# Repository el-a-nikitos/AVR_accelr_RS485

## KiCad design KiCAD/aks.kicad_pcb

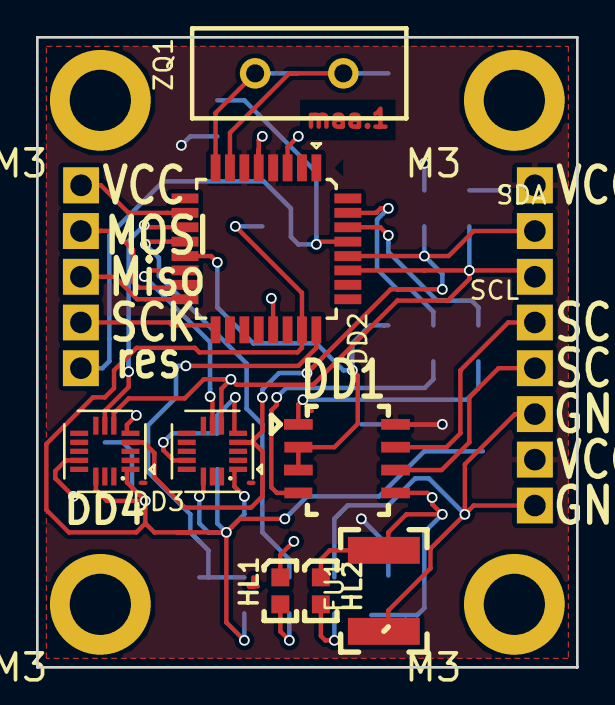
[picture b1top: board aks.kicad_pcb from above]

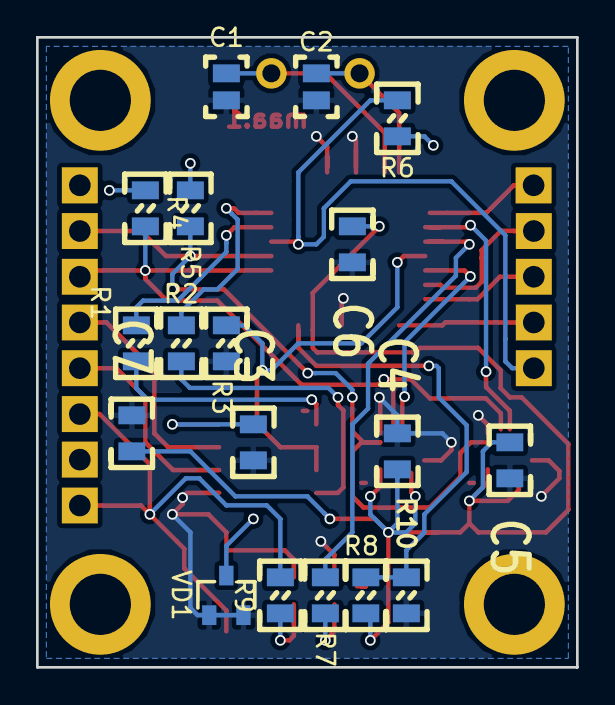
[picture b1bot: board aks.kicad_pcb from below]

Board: 2 copper layers, 30.0 x 35.0 mm, 43 parts (18 on the bottom side), 26 nets.

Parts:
C1, C2: К10-83-50В-12пФ; Конденсатор_SMD_К10-83(0603)
C3, C4, C5, C6, C7: К10-83-25В-4,7мкФ(2220); Конденсатор_SMD_0805
DD1: 5559ИН10; SO-8_RS485_CAN_Milandr_OTK
DD2: ATmega8; микросхема_ATMEGA-8-161AU
DD3, DD4: LIS3DH; акселерометр
FU1: Р1-8В-0.25-20K; Предохранитель_SMD(1812)
HL1, HL2: Светодиод_3Л341Е; Светодиод_SMD_0603
M3, M3#2, M3#3, M3#4: Отверстие_М3_под_гровер
R1, R2, R3, R4, R5, R6, R9: Р1-8В-0.125-20к; Резистор_SMD_0805_0,125Вт
R7: Р1-8В-0.125; Резистор_SMD_0805_0,125Вт
R8, R10: Резистор_0,125Вт; Резистор_SMD_0805_0,125Вт
VD1: Диод_КД257А; Диод_BAR43CFILM_SOT-23
XS1, XS11, XS12: VCC; Отверстие_под_пайку_D1.2
XS2, XS13: GND; Отверстие_под_пайку_D1.2
XS3: MOSI; Отверстие_под_пайку_D1.2
XS4: Miso; Отверстие_под_пайку_D1.2
XS5, XS6, XS7: SCK; Отверстие_под_пайку_D1.2
XS8: res; Отверстие_под_пайку_D1.2
XS9: SDA; Отверстие_под_пайку_D1.2
XS10: SCL; Отверстие_под_пайку_D1.2
ZQ1: РК456МДУ; Резонатор_РК456МДУ(DIP)

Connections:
A: DD1.6, XS6.1
B: DD1.7, XS7.1
EN: DD1.2, DD1.3, DD2.13, R3.2
EN1: DD2.10, XS11.1
Ep: C3.1, DD1.8, DD2.4, DD2.6, R4.1, R5.1, R6.2, VD1.2, XS1.1, XS12.1
GND: C1.1, C2.1, C3.2, C4.1, C5.1, C6.1, C7.1, DD1.5, DD2.3, DD2.5, DD2.21, DD3.5, DD3.12, DD4.5, DD4.12, FU1.1, HL1.2, HL2.2, R3.1, R10.2, VD1.1
GND_in: FU1.2, R9.1, XS2.1, XS13.1
HL1: DD2.12, R7.1
MISO: DD2.16, XS4.1
MOSI: DD2.15, XS3.1
unnamed: C1.2, DD2.7, ZQ1.1
unnamed: C2.2, DD2.8, ZQ1.2
unnamed: DD1.1, R1.1
unnamed: DD1.4, R2.1
unnamed: DD2.24, R8.2, R10.1
unnamed: HL1.1, R7.2
unnamed: HL2.1, R9.2
PB2: DD2.14, DD3.7
PD7: DD2.11, DD4.7
RX: DD2.30, R1.2
SCK: DD2.17, XS5.1
SCL: DD2.28, DD3.4, DD4.4, R5.2, XS9.1
SDA: DD2.27, DD3.6, DD4.6, R4.2, XS10.1
TX: DD2.31, R2.2
VCC: C4.2, C5.2, C6.2, C7.2, DD2.23, DD3.1, DD3.14, DD4.1, DD4.14, R8.1
reset: DD2.29, R6.1, XS8.1

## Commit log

2018-11-28 добавлен проект в KiCAD
2018-11-29 подготовлены GERBER файлы, exel-заказа не заполнена
2018-11-29 сформирован заказ для изготовления Резонит
2018-12-02 Список
2018-12-07 добавлены STL первой верии корпуса
2018-12-08 бодавлен банк библиотек ардуино, добавлен тестовый ардуино проект
2018-12-09 подготовлен кастомный проект опроса акселерометра с ардуины
2018-12-10 добавлены результаты измерений с/без конденсаторов
2018-12-28 добавлен прототип ТУ и структура кастомного ТУ
2018-12-28 3D компас - корпус акслерометра
2018-12-29 корректировка содержания и первого листа
2019-01-03 добавлен проект в Atmel Studio, реализована мигалка
2019-01-11 отлажен UART(RS485), I2C не работает
2019-01-12 папки структурированы, начата самописная библиотке TWI
2019-01-13 добавлен отдельный проект для ардуино - запрос ID устройства
2019-01-13 из проекта убрана связи по i2c - подготовлен для тестирования с arduio
2019-01-13 немного структурных причесываний
    добавлена, но не отлажена библиотека программного i2c
    изменено расположение терминала
    изменено название функций библиотек UART
2019-01-15 побежден i2c
    -библиотека с функцией записи и функцией чтения
    -в main успешный запрос регистра WhoAmI
2019-01-16 добавлен проект processing на монитор акселерометра
2019-01-18 в проекте processng нет корректировки по коэффициенту
2019-02-15 изменен акселерометр
2019-02-15 добавлена этикетка - не закончеа
2019-02-18 добавлена этикетка
2019-02-25 25.02
2019-02-27 ТУ не закончена
2019-03-03 ЭТ и ТУ
    в этикетке изменен индекс этикетке
    в ТУ заполнен 1й раздел (еще требует правок)
2019-03-04 начат раздел 3 - правила приемки
2019-03-28 пруф работы атмеги8 под ардуино
2019-03-28 правила сертификации
2019-03-29 заготовки типового ТУ на платы и техпроцесса
2019-03-29 задифайнен проект ардуины
2019-04-01 осты на пайку
2019-04-07 добавлен проект для работы в arduino ide
2019-04-07 проект в arduino ide
    мерцание светодиодом
    попытка поросить канал АЦП
2019-06-29 этикетка pdf
